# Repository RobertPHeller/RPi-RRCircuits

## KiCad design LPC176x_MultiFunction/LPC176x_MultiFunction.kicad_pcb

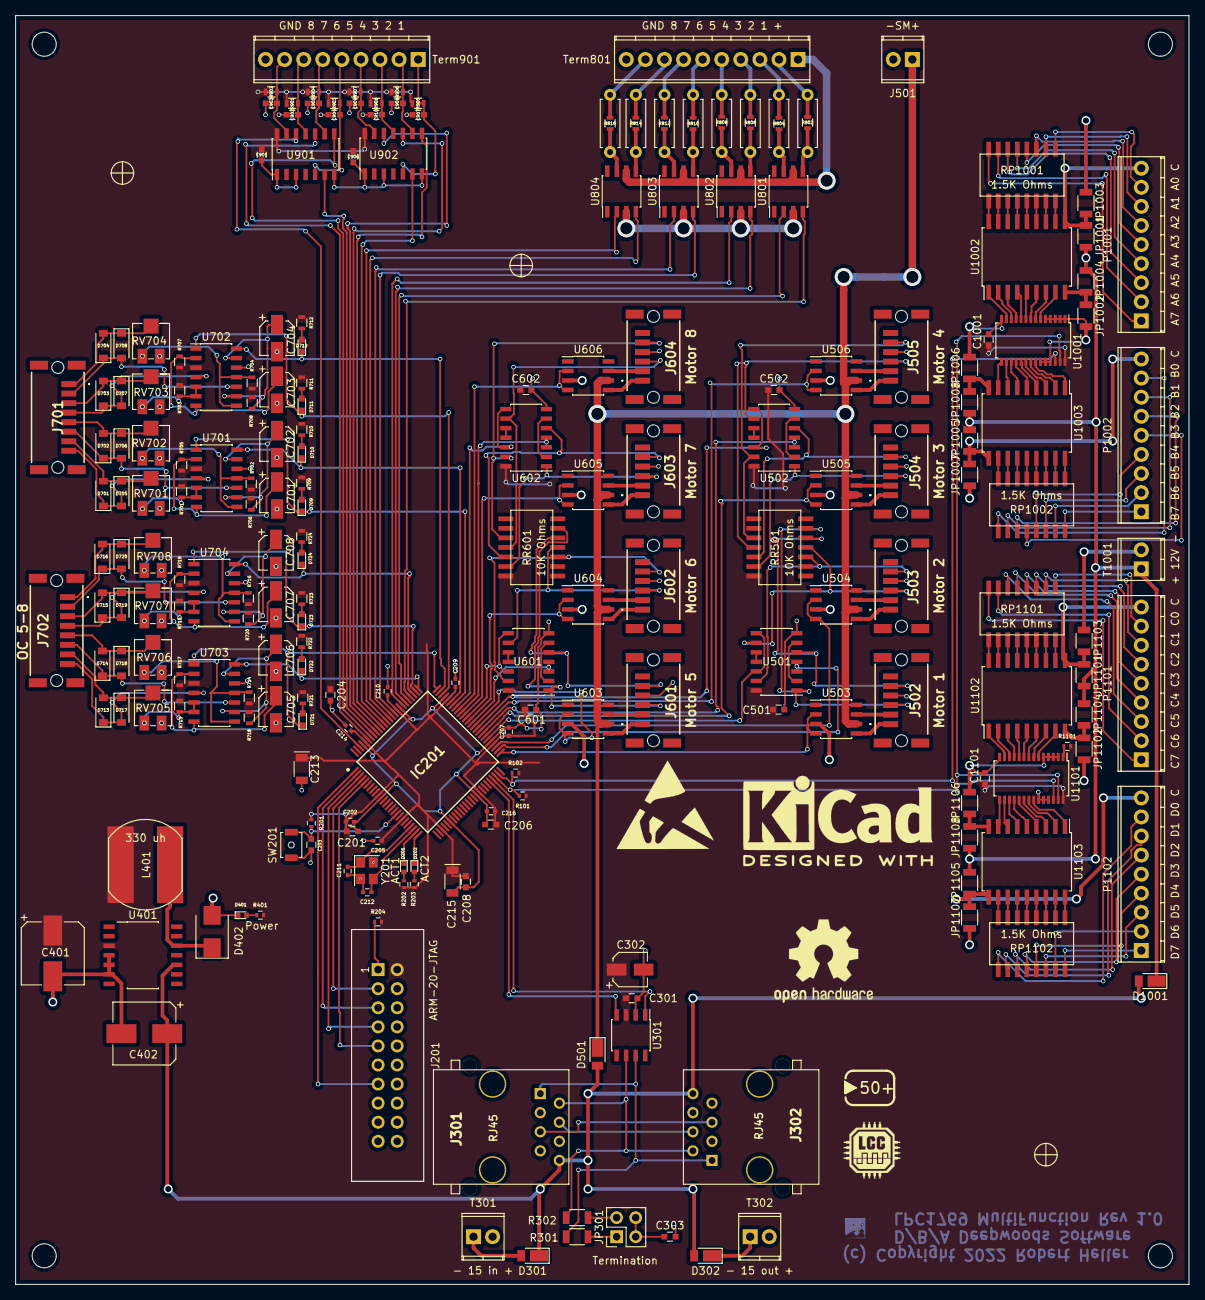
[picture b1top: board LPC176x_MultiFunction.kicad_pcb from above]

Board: 2 copper layers, 156.2 x 168.9 mm, 230 parts (0 on the bottom side), 283 nets.

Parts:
C201, C203, C204, C206, C208: 1uf; C_0603
C202, C205, C207, C209, C210, C214, C216: 100nf; C_0402
C211, C212: 18pf; C_0402
C213, C215: 10uf; C_POL_1206
C301, C501, C502, C601, C602, C901, C906, C1001, C1101: .1 uf; C_0603
C302: 15 uf 15V; CP_Elec_4x5.7
C303: 47 nf; C_0603
C401: 220 uf 25V; CP_Elec_8x10
C402: 22 uf 100V; CP_Elec_8x10
C701, C702, C703, C704, C705, C706, C707, C708: 2.2uf 50V; CP_Elec_4x5.7
C902, C903, C904, C905, C907, C908, C909, C910: 10 nf; C_0603
D201: ACT1; LED_0402
D202: ACT2; LED_0402
D301, D302, D501, D1001: DFLS240-7; D_PowerDI-123
D401: Power; LED_0402
D402: CMSH1-60 TR13; D_SMB
D701, D702, D703, D704, D705, D706, D707, D708, D713, D714, D715, D716, D717, D718, D719, D720: 1N4148; D_SOD-123
D709, D710, D711, D712, D721, D722, D723, D724: LED; LED_0603
FD101, FD102, FD103: Fudicial; Fiducial_classic_Small_SilkscreenTop_Type1
IC201: LPC1768FBD100K; QFP50P1600X1600X160-100N
J201: ARM-20-JTAG; IDC_Header_Straight_20pins
J301, J302: RJ45; RJ45_8N-S
J501: -SM+; TerminalBlock_Pheonix_MPT-2.54mm_2pol
J502: Motor 1; 474817
J503: Motor 2; 474817
J504: Motor 3; 474817
J505: Motor 4; 474817
J601: Motor 5; 474817
J602: Motor 6; 474817
J603: Motor 7; 474817
J604: Motor 8; 474817
J701: OC 1-4; 474818
J702: OC 5-8; 474818
JP301: Termination; Pin_Header_Straight_2x02_Pitch2.54mm
JP1001, JP1002, JP1003, JP1004, JP1005, JP1006, JP1007, JP1008, JP1101, JP1102, JP1103, JP1104, JP1105, JP1106, JP1107, JP1108: 0; R_1206
L401: 330 uh; SRN1060
MK101, MK102, MK103, MK104: Mounting_Hole; MountingHole_3.2mm_M3
P1001: A7 A6 A5 A4 A3 A2 A1 A0 C; TerminalBlock_Pheonix_MPT-2.54mm_9pol
P1002: B7 B6 B5 B4 B3 B2 B1 B0 C; TerminalBlock_Pheonix_MPT-2.54mm_9pol
P1101: C7 C6 C5 C4 C3 C2 C1 C0 C; TerminalBlock_Pheonix_MPT-2.54mm_9pol
P1102: D7 D6 D5 D4 D3 D2 D1 D0 C; TerminalBlock_Pheonix_MPT-2.54mm_9pol
R101, R102: 2.4K; R_0402
R201, R1101: 10K; R_0402
R202, R203: 270; R_0402
R204: 0; R_0402
R301, R302: 60 Ohms; R_1206
R401: 330; R_0402
R701, R702, R703, R704, R713, R714, R715, R716: 22K Ohms; R_0603
R705, R706, R707, R708, R717, R718, R719, R720: 1M Ohms; R_0603
R709, R710, R711, R712, R721, R722, R723, R724: 2.7K Ohms; R_0603
R801, R803, R805, R807, R809, R811, R813, R815: R; R_Axial_DIN0207_L6.3mm_D2.5mm_P7.62mm_Horizontal
R802, R804, R806, R808, R810, R812, R814, R816: 1.5K Ohms; R_0603
R901, R902, R903, R904, R905, R906, R907, R908: 10K Ohms; R_0603
RP1001, RP1002, RP1101, RP1102: 1.5K Ohms; 4816P
RR501, RR601: 10K Ohms; 4814P
RV701, RV702, RV703, RV704, RV705, RV706, RV707, RV708: 25K Ohms; Potentiometer_Trimmer_Bourns_3214J
SW201: RESET; SW_SPST_B3U-1000P-B
T301: - 15 in +; TerminalBlock_Pheonix_MPT-2.54mm_2pol
T302: - 15 out +; TerminalBlock_Pheonix_MPT-2.54mm_2pol
T1001: + 12V -; TerminalBlock_Pheonix_MPT-2.54mm_2pol
Term801: GND 8 7 6 5 4 3 2 1 +; TerminalBlock_Pheonix_MPT-2.54mm_10pol
Term901: GND 8 7 6 5 4 3 2 1; TerminalBlock_Pheonix_MPT-2.54mm_9pol
U301: TCAN332DR; SOIC-8_3.9x4.9mm_Pitch1.27mm
U401: LM2574N-3.3; SOIC-14_7.4x8.7mm_Pitch1.27mm
U501, U502, U601, U602: 74HCT00; SOIC-14_3.9x8.7mm_Pitch1.27mm
U503, U504, U505, U506, U603, U604, U605, U606: TC4428; SOIC-8_3.9x4.9mm_Pitch1.27mm
U701, U702, U703, U704: LM339; SOIC-14_3.9x8.7mm_Pitch1.27mm
U801, U802, U803, U804: TC4426; SOIC-8_3.9x4.9mm_Pitch1.27mm
U901, U902: 74HCT14; SOIC-14_3.9x8.7mm_Pitch1.27mm
U1001, U1101: PCA9685; TSSOP-28_4.4x9.7mm_Pitch0.65mm
U1002, U1003, U1102, U1103: TBD62X83A; SOIC-18W_7.5x11.6mm_Pitch1.27mm
Y201: 25Mhz; Crystal_SMD_Abracon_ABM8G-4pin_3.2x2.5mm

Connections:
+3V3: C201.1, C202.1, C204.1, C205.1, C206.1, C207.1, C208.1, C209.1, C210.1, C213.1, C214.1, C215.1, C216.1, C301.1, C302.1, C401.1, C501.1, C502.1, C601.1, C602.1, C901.1, C906.1, C1001.1, C1101.1, IC201.10, IC201.19, IC201.28, IC201.42, IC201.54, IC201.71, IC201.84, IC201.96, J201.2, L401.2, R101.1, R102.2, R201.1, R202.2, R203.2, R204.2, R401.2, R701.1, R702.1, R703.1, R704.1, R705.1, R706.1, R707.1, R708.1, R709.1, R710.1, R711.1, R712.1, R713.1, R714.1, R715.1, R716.1, R717.1, R718.1, R719.1, R720.1, R721.1, R722.1, R723.1, R724.1, R901.1, R902.1, R903.1, R904.1, R905.1, R906.1, R907.1, R908.1, R1101.2, RR501.14, RR601.14, U301.3, U401.3, U501.14, U502.14, U601.14, U602.14, U701.3, U702.3, U703.3, U704.3, U901.14, U902.14, U1001.28, U1101.28
+12V: D1001.1, JP1001.2, JP1004.1, JP1005.2, JP1008.1, JP1101.2, JP1104.1, JP1105.2, JP1108.1, T1001.1
/Buttons/Button1: IC201.89, U902.6
/Buttons/Button2: IC201.90, U902.8
/Buttons/Button3: IC201.91, U902.10
/Buttons/Button4: IC201.92, U902.12
/Buttons/Button5: IC201.93, U901.6
/Buttons/Button6: IC201.94, U901.8
/Buttons/Button7: IC201.95, U901.10
/Buttons/Button8: IC201.98, U901.12
/CAN Transciver/CANH: J301.1, J302.1, R301.1, U301.7
/CAN Transciver/CANL: J301.2, J302.2, R302.1, U301.6
/CAN Transciver/CAN_RX: IC201.46, U301.4
/CAN Transciver/CAN_TX: IC201.47, U301.1
/LED / Drivers/LED1: IC201.79, U801.4
/LED / Drivers/LED2: IC201.80, U801.2
/LED / Drivers/LED3: IC201.81, U802.4
/LED / Drivers/LED4: IC201.82, U802.2
/LED / Drivers/LED5: IC201.85, U803.4
/LED / Drivers/LED6: IC201.86, U803.2
/LED / Drivers/LED7: IC201.87, U804.4
/LED / Drivers/LED8: IC201.88, U804.2
/MCU/Motor1: IC201.51, U503.2, U503.4
/MCU/Motor2: IC201.53, U504.2, U504.4
/MCU/Motor3: IC201.57, U505.2, U505.4
/MCU/Motor4: IC201.59, U506.2, U506.4
/MCU/Motor5: IC201.61, U603.2, U603.4
/MCU/Motor6: IC201.63, U604.2, U604.4
/MCU/Motor7: IC201.65, U605.2, U605.4
/MCU/Motor8: IC201.67, U606.2, U606.4
/MCU/OD1: D709.1, IC201.69, U701.1
/MCU/OD2: D710.1, IC201.70, U701.14
/MCU/OD3: D711.1, IC201.73, U702.1
/MCU/OD4: D712.1, IC201.74, U702.14
/MCU/OD5: D721.1, IC201.75, U703.1
/MCU/OD6: D722.1, IC201.76, U703.14
/MCU/OD7: D723.1, IC201.77, U704.1
/MCU/OD8: D724.1, IC201.78, U704.14
/MCU/Points1: IC201.52, U501.3, U501.4
/MCU/Points2: IC201.56, U501.8, U501.12
/MCU/Points3: IC201.58, U502.3, U502.4
/MCU/Points4: IC201.60, U502.8, U502.12
/MCU/Points5: IC201.62, U601.3, U601.4
/MCU/Points6: IC201.64, U601.8, U601.12
/MCU/Points7: IC201.66, U602.3, U602.4
/MCU/Points8: IC201.68, U602.8, U602.12
/MCU/SCL: IC201.49, R102.1, U1001.26, U1101.26
/MCU/SDA: IC201.48, R101.2, U1001.27, U1101.27
/Stall Motors 1/M1A: J502.1, U503.5
/Stall Motors 1/M1B: J502.2, U503.7
/Stall Motors 1/M2A: J503.1, U504.5
/Stall Motors 1/M2B: J503.2, U504.7
/Stall Motors 1/M3A: J504.1, U505.5
/Stall Motors 1/M3B: J504.2, U505.7
/Stall Motors 1/M4A: J505.1, U506.5
/Stall Motors 1/M4B: J505.2, U506.7
/Stall Motors 1/P1A: J502.3, RR501.6, U501.1
/Stall Motors 1/P1B: J502.5, RR501.5, U501.5
/Stall Motors 1/P2A: J503.3, RR501.4, U501.9
/Stall Motors 1/P2B: J503.5, RR501.3, U501.13
/Stall Motors 1/P3A: J504.3, RR501.13, U502.1
/Stall Motors 1/P3B: J504.5, RR501.12, U502.5
/Stall Motors 1/P4A: J505.3, RR501.11, U502.9
/Stall Motors 1/P4B: J505.5, RR501.10, U502.13
/Stall Motors 2/M5A: J601.1, U603.5
/Stall Motors 2/M5B: J601.2, U603.7
/Stall Motors 2/M6A: J602.1, U604.5
/Stall Motors 2/M6B: J602.2, U604.7
/Stall Motors 2/M7A: J603.1, U605.5
/Stall Motors 2/M7B: J603.2, U605.7
/Stall Motors 2/M8A: J604.1, U606.5
/Stall Motors 2/M8B: J604.2, U606.7
/Stall Motors 2/P5A: J601.3, RR601.6, U601.1
/Stall Motors 2/P5B: J601.5, RR601.5, U601.5
/Stall Motors 2/P6A: J602.3, RR601.4, U601.9
/Stall Motors 2/P6B: J602.5, RR601.3, U601.13
/Stall Motors 2/P7A: J603.3, RR601.13, U602.1
/Stall Motors 2/P7B: J603.5, RR601.12, U602.5
/Stall Motors 2/P8A: J604.3, RR601.11, U602.9
/Stall Motors 2/P8B: J604.5, RR601.10, U602.13
CAN +12V: C402.1, D301.1, D302.2, D501.2, D1001.2, J301.8, J302.8, U401.10
GND: C201.2, C202.2, C203.2, C204.2, C205.2, C206.2, C207.2, C208.2, C209.2, C210.2, C211.2, C212.2, C213.2, C214.2, C215.2, C216.2, C301.2, C302.2, C303.2, C401.2, C402.2, C501.2, C502.2, C601.2, C602.2, C701.2, C702.2, C703.2, C704.2, C705.2, C706.2, C707.2, C708.2, C901.2, C902.2, C903.2, C904.2, C905.2, C906.2, C907.2, C908.2, C909.2, C910.2, C1001.2, C1101.2, D401.1, D402.2, IC201.11, IC201.31, IC201.41, IC201.55, IC201.72, IC201.83, IC201.97, J201.4, J201.6, J201.8, J201.10, J201.12, J201.14, J201.16, J201.18, J201.20, J301.3, J301.6, J301.7, J302.3, J302.6, J302.7, J501.2, J502.4, J503.4, J504.4, J505.4, J601.4, J602.4, J603.4, J604.4, JP1002.2, JP1003.1, JP1006.2, JP1007.1, JP1102.2, JP1103.1, JP1106.2, JP1107.1, RV701.1, RV702.1, RV703.1, RV704.1, RV705.1, RV706.1, RV707.1, RV708.1, SW201.1, T301.2, T302.2, T1001.2, Term801.10, Term901.9, U301.2, U401.4, U401.5, U401.6, U501.7, U502.7, U503.3, U504.3, U505.3, U506.3, U601.7, U602.7, U603.3, U604.3, U605.3, U606.3, U701.12, U702.12, U703.12, U704.12, U801.3, U802.3, U803.3, U804.3, U901.1, U901.3, U901.7, U902.1, U902.3, U902.7, U1001.1, U1001.2, U1001.3, U1001.4, U1001.5, U1001.14, U1001.23, U1001.24, U1001.25, U1101.2, U1101.3, U1101.4, U1101.5, U1101.14, U1101.23, U1101.24, U1101.25, Y201.2, Y201.4
unnamed: C203.1, IC201.17, R201.2, SW201.2
unnamed: C211.1, IC201.22, Y201.1
unnamed: C212.1, IC201.23, Y201.3
unnamed: C303.1, JP301.3, JP301.4
unnamed: C701.1, R705.2, U701.2, U701.7
unnamed: C702.1, R706.2, U701.9, U701.13
unnamed: C703.1, R707.2, U702.2, U702.7
unnamed: C704.1, R708.2, U702.9, U702.13
unnamed: C705.1, R717.2, U703.2, U703.7
unnamed: C706.1, R718.2, U703.9, U703.13
unnamed: C707.1, R719.2, U704.2, U704.7
unnamed: C708.1, R720.2, U704.9, U704.13
unnamed: C902.1, R901.2, Term901.7, U901.11
unnamed: C903.1, R902.2, Term901.8, U901.13
unnamed: C904.1, R903.2, Term901.5, U901.5
unnamed: C905.1, R904.2, Term901.6, U901.9
unnamed: C907.1, R905.2, Term901.1, U902.5
unnamed: C908.1, R906.2, Term901.2, U902.9
unnamed: C909.1, R907.2, Term901.4, U902.13
unnamed: C910.1, R908.2, Term901.3, U902.11
unnamed: D201.1, IC201.24
unnamed: D201.2, R202.1
unnamed: D202.1, IC201.25
unnamed: D202.2, R203.1
unnamed: D301.2, T301.1
unnamed: D302.1, T302.1
unnamed: D401.2, R401.1
unnamed: D402.1, L401.1, U401.12
unnamed: D701.1, D705.2, J701.8, U701.4
unnamed: D701.2, D705.1, J701.7, RV701.2
unnamed: D702.1, D706.2, J701.6, U701.10
unnamed: D702.2, D706.1, J701.5, RV702.2
unnamed: D703.1, D707.2, J701.4, U702.4
unnamed: D703.2, D707.1, J701.3, RV703.2
unnamed: D704.1, D708.2, J701.2, U702.10
unnamed: D704.2, D708.1, J701.1, RV704.2
unnamed: D709.2, R709.2
unnamed: D710.2, R710.2
unnamed: D711.2, R711.2
unnamed: D712.2, R712.2
unnamed: D713.1, D717.2, J702.8, U703.4
unnamed: D713.2, D717.1, J702.7, RV705.2
unnamed: D714.1, D718.2, J702.6, U703.10
unnamed: D714.2, D718.1, J702.5, RV706.2
unnamed: D715.1, D719.2, J702.4, U704.4
unnamed: D715.2, D719.1, J702.3, RV707.2
unnamed: D716.1, D720.2, J702.2, U704.10
unnamed: D716.2, D720.1, J702.1, RV708.2
unnamed: D721.2, R721.2
unnamed: D722.2, R722.2
unnamed: D723.2, R723.2
unnamed: D724.2, R724.2
unnamed: IC201.1, J201.13
unnamed: IC201.2, J201.5
unnamed: IC201.3, J201.7
unnamed: IC201.4, J201.3
unnamed: IC201.5, J201.9
unnamed: J201.1, R204.1
unnamed: J301.4, J302.4
unnamed: J301.5, J302.5
unnamed: JP301.1, R301.2
unnamed: JP301.2, R302.2
unnamed: JP1001.1, JP1003.2, P1001.9, U1002.10
unnamed: JP1002.1, JP1004.2, U1002.9
unnamed: JP1005.1, JP1007.2, P1002.9, U1003.10
unnamed: JP1006.1, JP1008.2, U1003.9
unnamed: JP1101.1, JP1103.2, P1101.9, U1102.10
unnamed: JP1102.1, JP1104.2, U1102.9
unnamed: JP1105.1, JP1107.2, P1102.9, U1103.10
unnamed: JP1106.1, JP1108.2, U1103.9
unnamed: P1001.1, RP1001.16
unnamed: P1001.2, RP1001.15
unnamed: P1001.3, RP1001.14
unnamed: P1001.4, RP1001.13
unnamed: P1001.5, RP1001.12
unnamed: P1001.6, RP1001.11
unnamed: P1001.7, RP1001.10
unnamed: P1001.8, RP1001.9
unnamed: P1002.1, RP1002.16
unnamed: P1002.2, RP1002.15
unnamed: P1002.3, RP1002.14
unnamed: P1002.4, RP1002.13
unnamed: P1002.5, RP1002.12
unnamed: P1002.6, RP1002.11
unnamed: P1002.7, RP1002.10
unnamed: P1002.8, RP1002.9
unnamed: P1101.1, RP1101.16
unnamed: P1101.2, RP1101.15
unnamed: P1101.3, RP1101.14
unnamed: P1101.4, RP1101.13
unnamed: P1101.5, RP1101.12
unnamed: P1101.6, RP1101.11
unnamed: P1101.7, RP1101.10
unnamed: P1101.8, RP1101.9
unnamed: P1102.1, RP1102.16
unnamed: P1102.2, RP1102.15
unnamed: P1102.3, RP1102.14
unnamed: P1102.4, RP1102.13
unnamed: P1102.5, RP1102.12
unnamed: P1102.6, RP1102.11
unnamed: P1102.7, RP1102.10
unnamed: P1102.8, RP1102.9
unnamed: R701.2, RV701.3, U701.5, U701.6
unnamed: R702.2, RV702.3, U701.8, U701.11
unnamed: R703.2, RV703.3, U702.5, U702.6
unnamed: R704.2, RV704.3, U702.8, U702.11
unnamed: R713.2, RV705.3, U703.5, U703.6
unnamed: R714.2, RV706.3, U703.8, U703.11
unnamed: R715.2, RV707.3, U704.5, U704.6
unnamed: R716.2, RV708.3, U704.8, U704.11
unnamed: R801.1, R802.1, Term801.2
unnamed: R801.2, R802.2, U801.5
unnamed: R803.1, R804.1, Term801.3
unnamed: R803.2, R804.2, U801.7
unnamed: R805.1, R806.1, Term801.4
unnamed: R805.2, R806.2, U802.5
unnamed: R807.1, R808.1, Term801.5
unnamed: R807.2, R808.2, U802.7
unnamed: R809.1, R810.1, Term801.6
unnamed: R809.2, R810.2, U803.5
unnamed: R811.1, R812.1, Term801.7
unnamed: R811.2, R812.2, U803.7
unnamed: R813.1, R814.1, Term801.8
unnamed: R813.2, R814.2, U804.5
unnamed: R815.1, R816.1, Term801.9
unnamed: R815.2, R816.2, U804.7
unnamed: R1101.1, U1101.1
unnamed: RP1001.1, U1002.18
unnamed: RP1001.2, U1002.17
unnamed: RP1001.3, U1002.16
unnamed: RP1001.4, U1002.15
unnamed: RP1001.5, U1002.14
unnamed: RP1001.6, U1002.13
unnamed: RP1001.7, U1002.12
unnamed: RP1001.8, U1002.11
unnamed: RP1002.1, U1003.18
unnamed: RP1002.2, U1003.17
unnamed: RP1002.3, U1003.16
unnamed: RP1002.4, U1003.15
unnamed: RP1002.5, U1003.14
unnamed: RP1002.6, U1003.13
unnamed: RP1002.7, U1003.12
unnamed: RP1002.8, U1003.11
unnamed: RP1101.1, U1102.18
unnamed: RP1101.2, U1102.17
unnamed: RP1101.3, U1102.16
unnamed: RP1101.4, U1102.15
unnamed: RP1101.5, U1102.14
unnamed: RP1101.6, U1102.13
unnamed: RP1101.7, U1102.12
unnamed: RP1101.8, U1102.11
unnamed: RP1102.1, U1103.18
unnamed: RP1102.2, U1103.17
unnamed: RP1102.3, U1103.16
unnamed: RP1102.4, U1103.15
unnamed: RP1102.5, U1103.14
unnamed: RP1102.6, U1103.13
unnamed: RP1102.7, U1103.12
unnamed: RP1102.8, U1103.11
unnamed: U501.2, U501.6
unnamed: U501.10, U501.11
unnamed: U502.2, U502.6
unnamed: U502.10, U502.11
unnamed: U601.2, U601.6
unnamed: U601.10, U601.11
unnamed: U602.2, U602.6
unnamed: U602.10, U602.11
unnamed: U1001.6, U1002.8
unnamed: U1001.7, U1002.7
unnamed: U1001.8, U1002.6
unnamed: U1001.9, U1002.5
unnamed: U1001.10, U1002.4
unnamed: U1001.11, U1002.3
unnamed: U1001.12, U1002.2
unnamed: U1001.13, U1002.1
unnamed: U1001.15, U1003.8
unnamed: U1001.16, U1003.7
unnamed: U1001.17, U1003.6
unnamed: U1001.18, U1003.5
unnamed: U1001.19, U1003.4
unnamed: U1001.20, U1003.3
unnamed: U1001.21, U1003.2
unnamed: U1001.22, U1003.1
unnamed: U1101.6, U1102.8
unnamed: U1101.7, U1102.7
unnamed: U1101.8, U1102.6
unnamed: U1101.9, U1102.5
unnamed: U1101.10, U1102.4
unnamed: U1101.11, U1102.3
unnamed: U1101.12, U1102.2
unnamed: U1101.13, U1102.1
unnamed: U1101.15, U1103.8
unnamed: U1101.16, U1103.7
unnamed: U1101.17, U1103.6
unnamed: U1101.18, U1103.5
unnamed: U1101.19, U1103.4
unnamed: U1101.20, U1103.3
unnamed: U1101.21, U1103.2
unnamed: U1101.22, U1103.1
SMPower: D501.1, J501.1, U503.6, U504.6, U505.6, U506.6, U603.6, U604.6, U605.6, U606.6
VPower: Term801.1, U801.6, U802.6, U803.6, U804.6

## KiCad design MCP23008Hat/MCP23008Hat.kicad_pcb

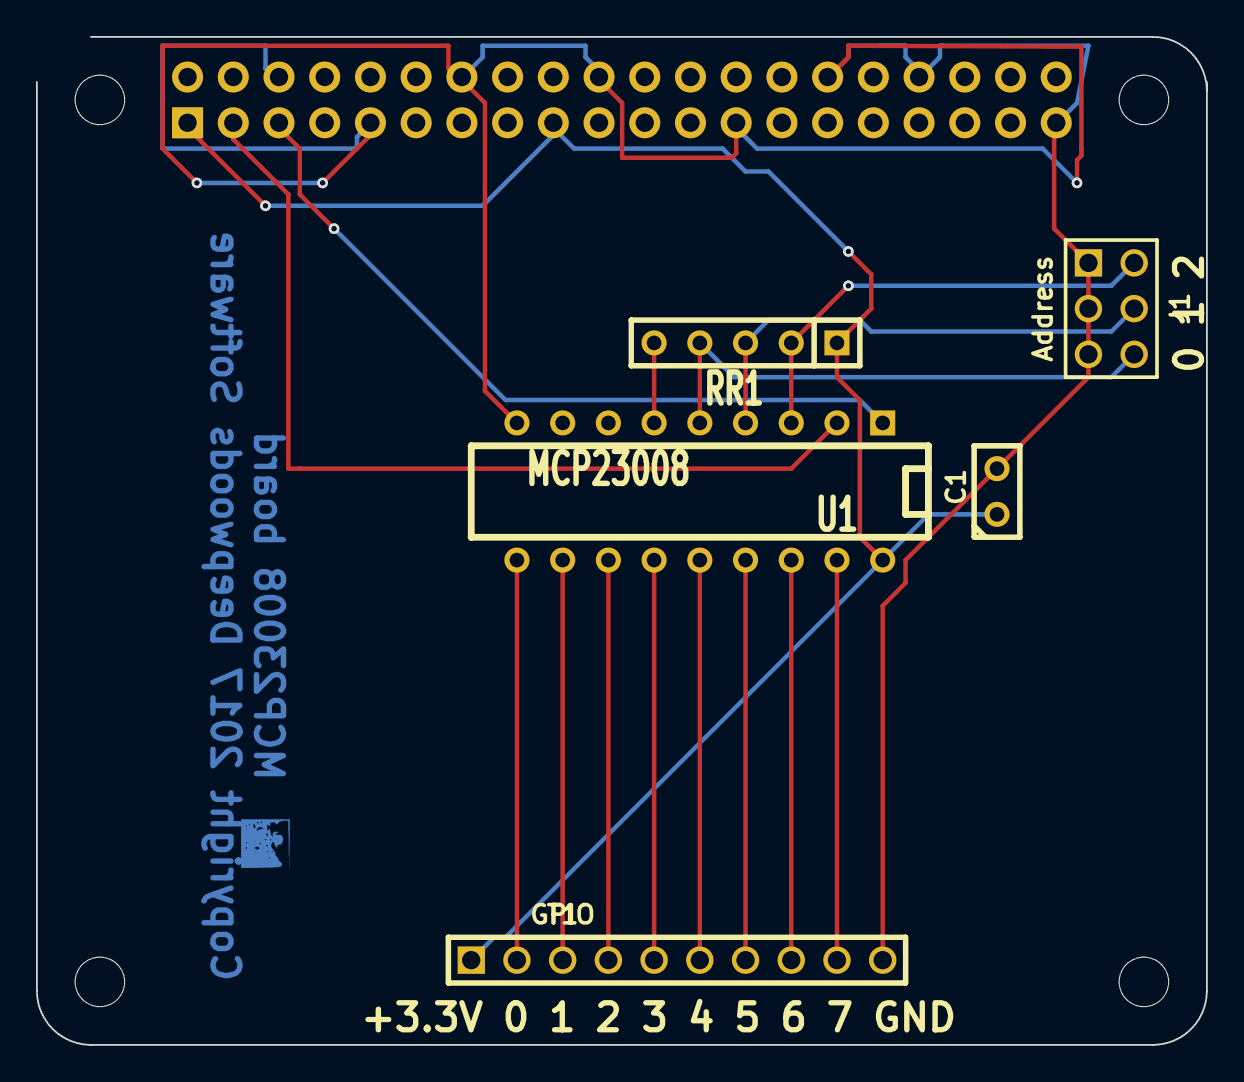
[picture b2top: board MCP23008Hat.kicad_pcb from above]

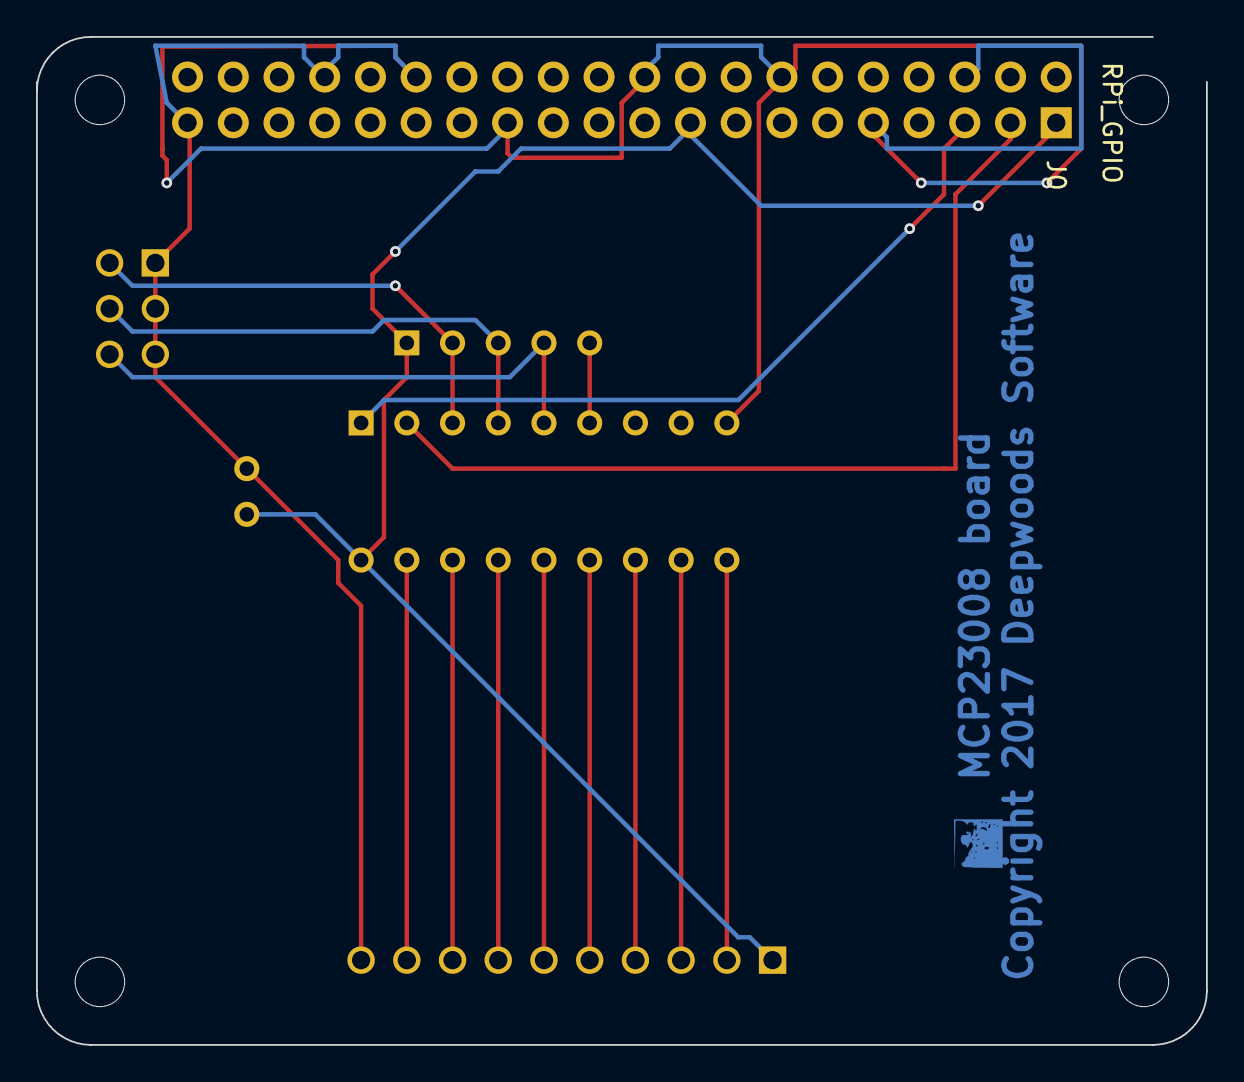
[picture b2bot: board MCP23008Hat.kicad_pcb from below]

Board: 2 copper layers, 65.0 x 56.0 mm, 10 parts (5 on the bottom side), 12 nets.

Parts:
C1: .1 uf; C1
H1, H2, H3, H4: RPi_Hat_Mounting_Hole
J0: RPi_GPIO; Pin_Header_Straight_2x20
J1: Address; pin_array_3x2
RR1: 10K Ohms; SIL-5
T1: GPIO; PIN_ARRAY_5x1
U1: MCP23008; DIP-18__300

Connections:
+3.3V: C1.1, J0.1, J0.17, RR1.1, T1.1, U1.18
/SCL: J0.5, U1.1
/SDA: J0.3, U1.2
GND: C1.2, J0.6, J0.9, J0.14, J0.20, J0.25, J0.30, J0.34, J0.39, J1.1, J1.3, J1.5, U1.9
unnamed: RR1.5, U1.6
unnamed: J1.2, RR1.2, U1.3
unnamed: J1.4, RR1.3, U1.4
unnamed: J1.6, RR1.4, U1.5
unnamed: T1.2, U1.10
unnamed: T1.3, U1.11
unnamed: T1.4, U1.12
unnamed: T1.5, U1.13

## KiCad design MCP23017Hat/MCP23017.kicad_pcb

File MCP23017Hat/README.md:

# MCP23017Hat

This is a 16 pin I2C port expander using a MCP230017.

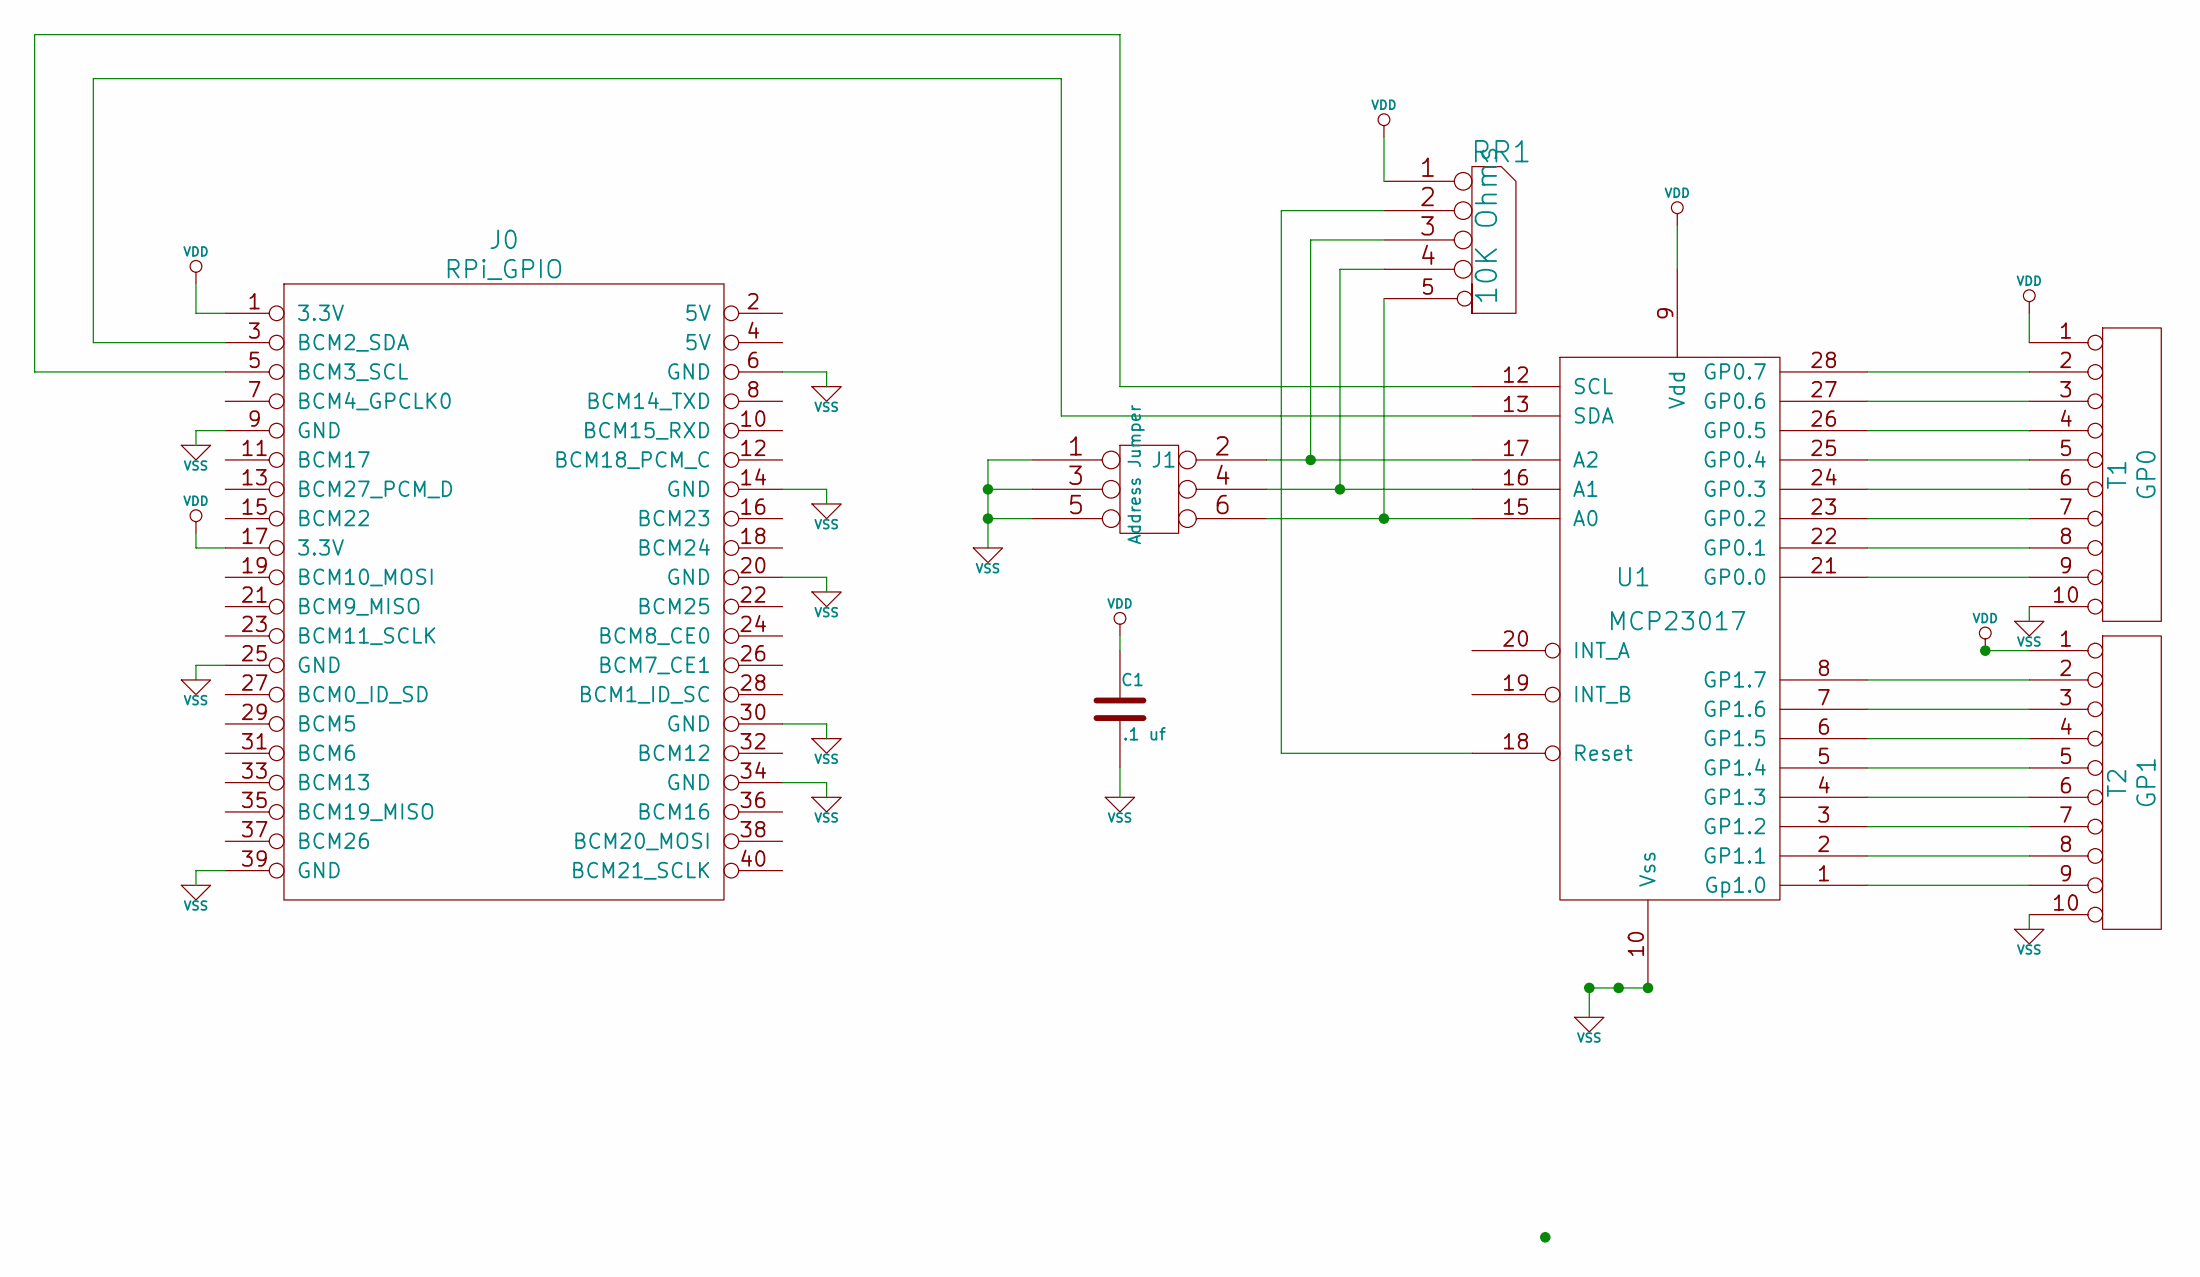
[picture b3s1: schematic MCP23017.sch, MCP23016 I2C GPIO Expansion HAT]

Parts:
C1: .1 uf; Mouser Part Number 21RZ310-RC
J0: RPi_GPIO; Pin_Header_Straight_2x20; Mouser Part Number 855-M20-6102045
J1: Address Jumper; pin_array_3x2; Mouser Part Number 517-929836-02-03
RR1: 10K Ohms; Mouser Part Number 652-4605X-1LF-10K
T1: GP0; SIL-10; Mouser Part Number 651-1725737
T2: GP1; SIL-10; Mouser part Number 651-1725737
U1: MCP23017; Mouser part Number 579-MCP23017-E/SP

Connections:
unnamed: T1.9, U1.21 (GP0.0)
unnamed: T2.2, U1.8 (GP1.7)
unnamed: T2.3, U1.7 (GP1.6)
unnamed: T2.4, U1.6 (GP1.5)
unnamed: T2.5, U1.5 (GP1.4)
unnamed: T2.6, U1.4 (GP1.3)
unnamed: T2.7, U1.3 (GP1.2)
unnamed: T2.8, U1.2 (GP1.1)
unnamed: T2.9, U1.1 (Gp1.0)
unnamed: T1.2, U1.28 (GP0.7)
unnamed: T1.3, U1.27 (GP0.6)
unnamed: T1.4, U1.26 (GP0.5)
unnamed: T1.5, U1.25 (GP0.4)
unnamed: T1.6, U1.24 (GP0.3)
unnamed: T1.7, U1.23 (GP0.2)
unnamed: J0.5 (BCM3_SCL), U1.12 (SCL)
unnamed: J0.3 (BCM2_SDA), U1.13 (SDA)
unnamed: T1.8, U1.22 (GP0.1)
unnamed: RR1.2, U1.18 (Reset)
unnamed: J1.2, RR1.3, U1.17 (A2)
unnamed: J1.4, RR1.4, U1.16 (A1)
unnamed: J1.6, RR1.5, U1.15 (A0)
VDD: C1.1, J0.1 (3.3V), J0.17 (3.3V), RR1.1 (COM), T1.1, T2.1, U1.9 (Vdd)
VSS: C1.2, J0.6 (GND), J0.9 (GND), J0.14 (GND), J0.20 (GND), J0.25 (GND), J0.30 (GND), J0.34 (GND), J0.39 (GND), J1.1, J1.3, J1.5, T1.10, T2.10, U1.10 (Vss)

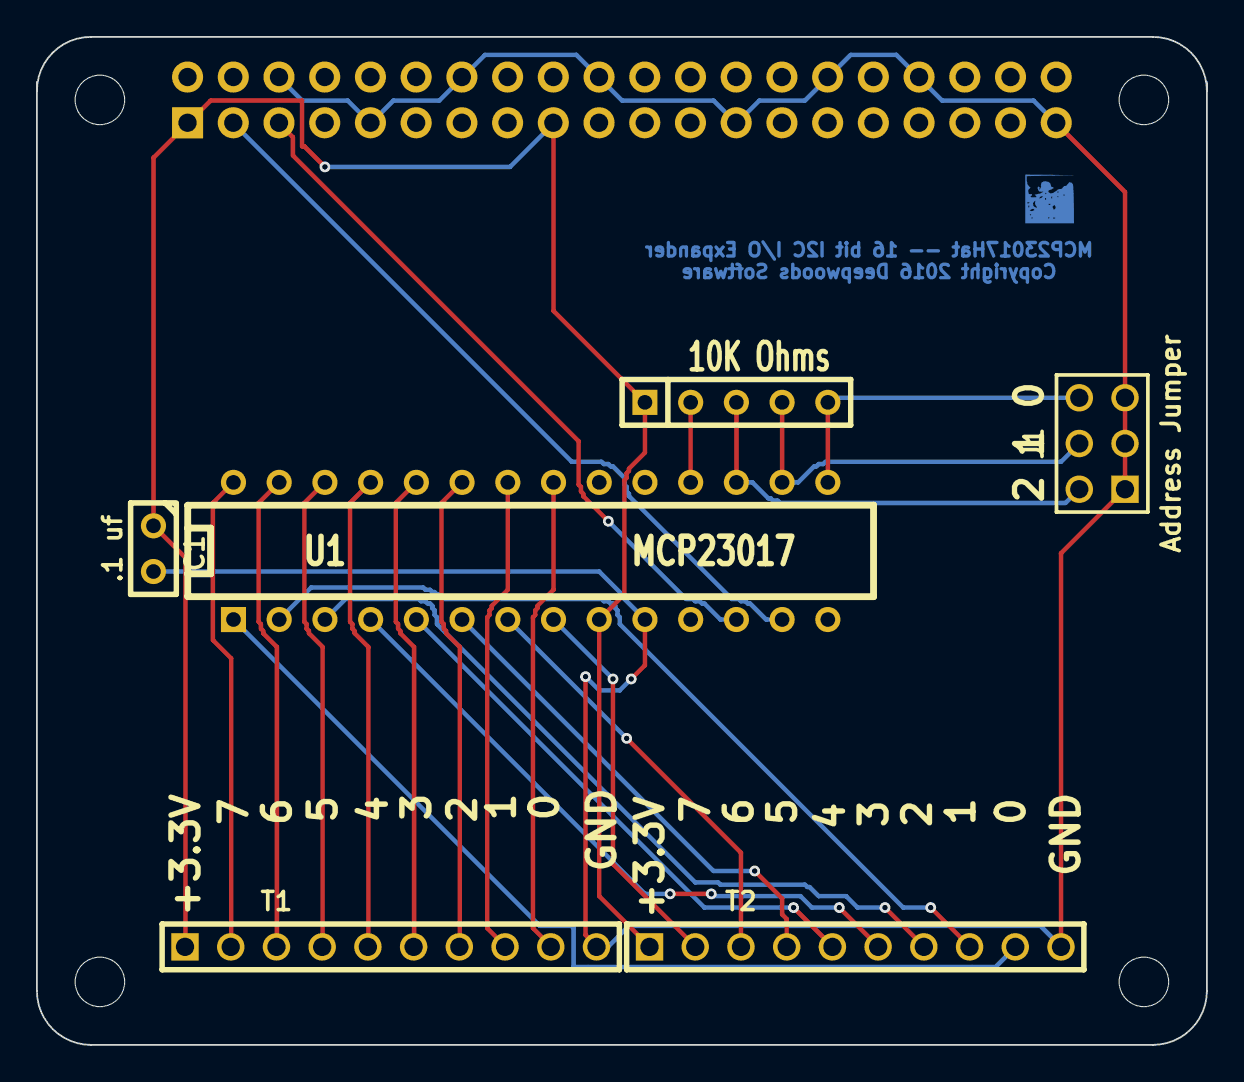
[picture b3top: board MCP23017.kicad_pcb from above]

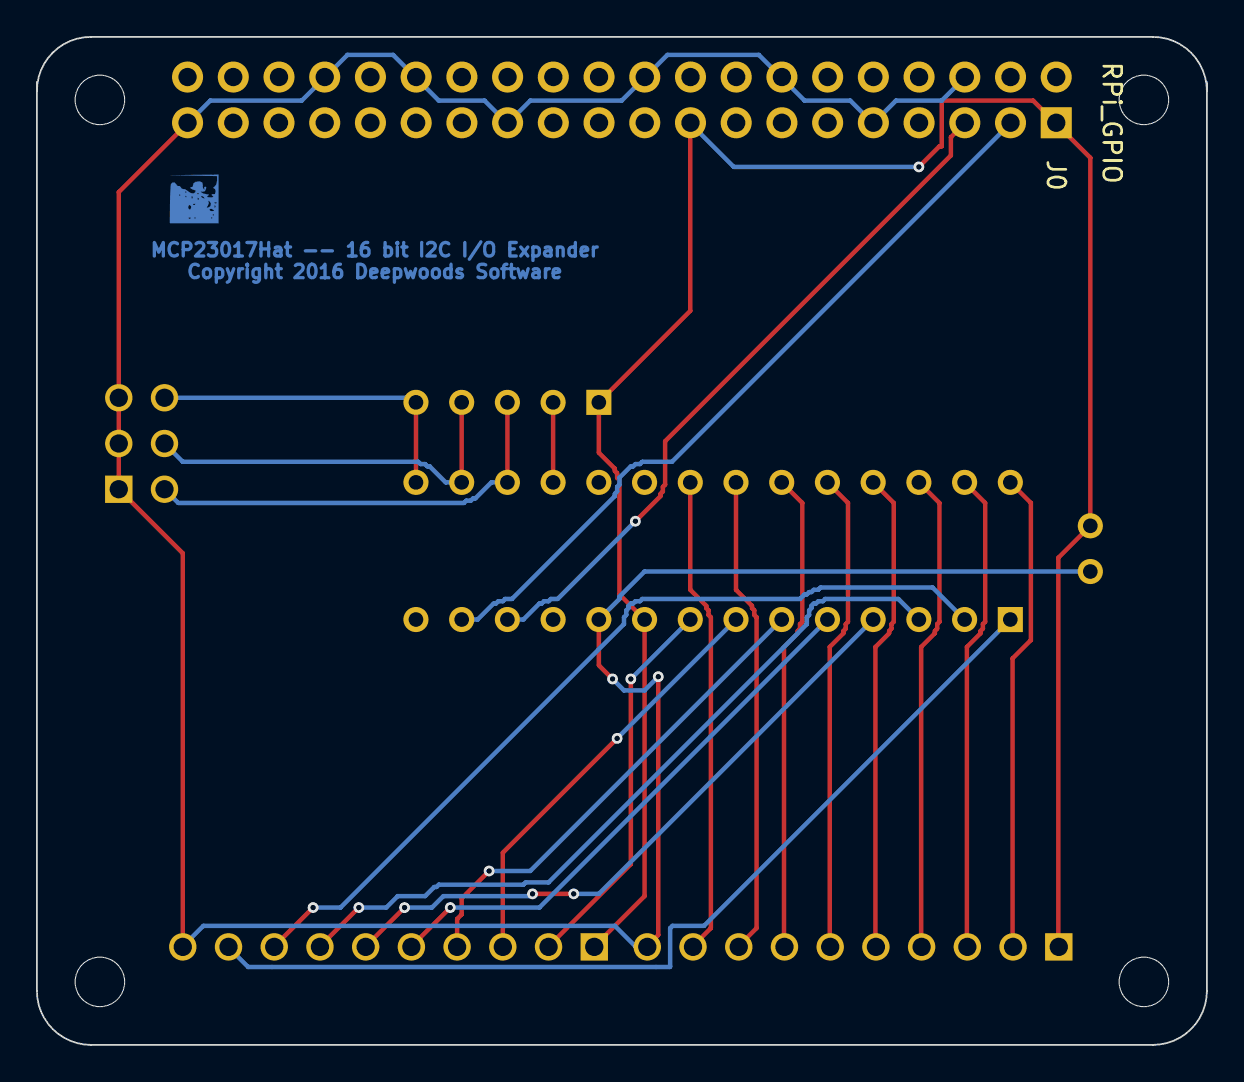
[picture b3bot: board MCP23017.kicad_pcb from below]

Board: 2 copper layers, 65.0 x 56.0 mm, 11 parts (5 on the bottom side), 24 nets.

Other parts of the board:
H1, H2, H3, H4: RPi_Hat_Mounting_Hole

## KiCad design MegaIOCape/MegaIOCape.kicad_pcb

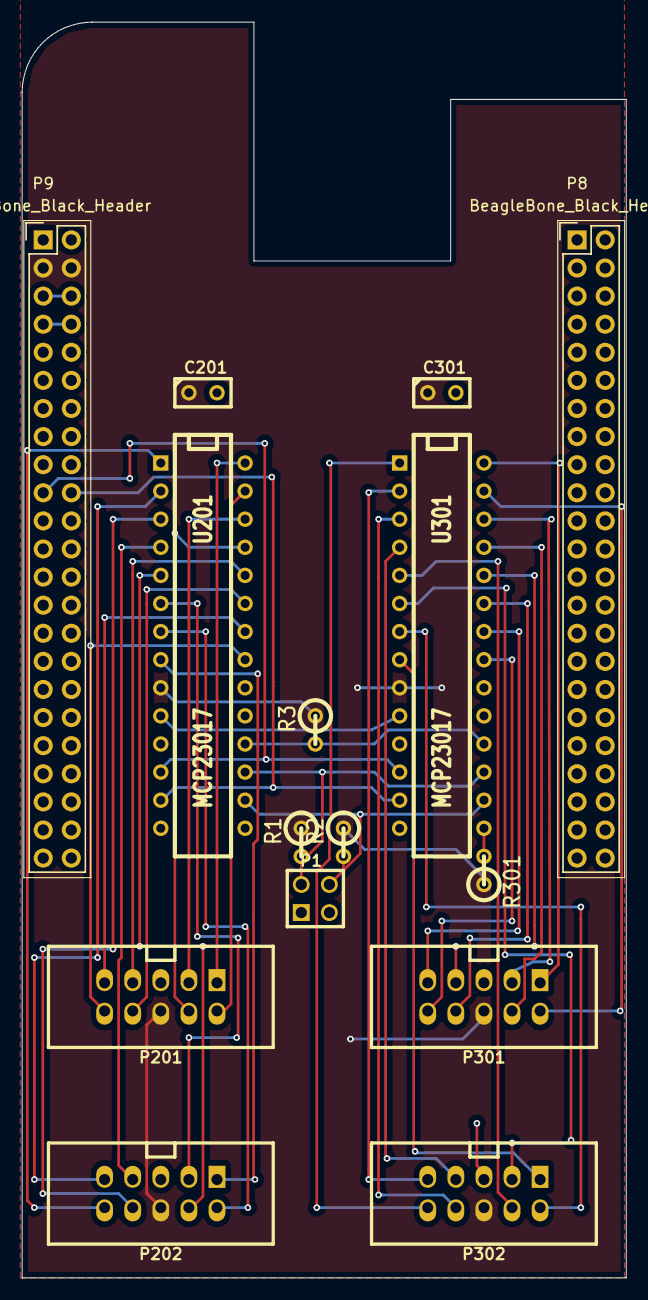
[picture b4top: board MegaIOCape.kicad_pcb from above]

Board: 2 copper layers, 54.6 x 113.5 mm, 15 parts (0 on the bottom side), 42 nets.

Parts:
C201, C301: .1 uf; C1
P1: 0 1; PIN_ARRAY_2X2
P8, P9: BeagleBone_Black_Header; Socket_BeagleBone_Black
P201: GPIO 1; vasch_strip_5x2
P202: GPIO 2; vasch_strip_5x2
P301: GPIO 3; vasch_strip_5x2
P302: GPIO 4; vasch_strip_5x2
R1, R2, R3, R301: 10K Ohms; R1
U201, U301: MCP23017; DIP-28__300

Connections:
3V3: C201.1, C301.1, P9.3, P9.4, P201.6, P202.6, P301.6, P302.6, R1.1, R2.1, R3.1, R301.1, U201.9, U301.9
+5V: P9.5, P9.6
/MCP23017 1/A0: P1.4, R2.2, U201.16, U301.16
/MCP23017 1/A1: P1.2, R1.2, U201.17, U301.17
/MCP23017 1/Reset: R3.2, U201.18, U301.18
/MCP23017 1/SCL: P9.19, U201.12, U301.12
/MCP23017 1/SDA: P9.20, U201.13, U301.13
GND: C201.2, C301.2, P1.1, P1.3, P8.1, P8.2, P9.1, P9.2, P9.43, P9.44, P9.45, P9.46, P201.5, P202.5, P301.5, P302.5, U201.10, U201.15, U301.10
unnamed: P201.4, U201.25
unnamed: P201.10, U201.21
unnamed: P201.9, U201.22
unnamed: P201.8, U201.23
unnamed: P201.7, U201.24
unnamed: P201.3, U201.26
unnamed: P201.2, U201.27
unnamed: P201.1, U201.28
unnamed: P202.4, U201.5
unnamed: P202.3, U201.6
unnamed: P202.7, U201.4
unnamed: P202.8, U201.3
unnamed: P202.9, U201.2
unnamed: P202.10, U201.1
unnamed: P202.2, U201.7
unnamed: P202.1, U201.8
unnamed: P301.9, U301.22
unnamed: P301.8, U301.23
unnamed: P301.7, U301.24
unnamed: P301.10, U301.21
unnamed: P301.4, U301.25
unnamed: P301.3, U301.26
unnamed: P301.2, U301.27
unnamed: P301.1, U301.28
unnamed: R301.2, U301.15
unnamed: P302.4, U301.5
unnamed: P302.3, U301.6
unnamed: P302.7, U301.4
unnamed: P302.8, U301.3
unnamed: P302.9, U301.2
unnamed: P302.10, U301.1
unnamed: P302.2, U301.7
unnamed: P302.1, U301.8
SYS_5V: P9.7, P9.8

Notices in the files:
LPC176x_MultiFunction/LPC176x_MultiFunction.kicad_pcb:
(c) Copyright 2022 Robert Heller
MCP23008Hat/MCP23008Hat.kicad_pcb:
Copyright 2017 Deepwoods Software
MCP23017Hat/MCP23017.kicad_pcb:
Copyright 2016 Deepwoods Software
